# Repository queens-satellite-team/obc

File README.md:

# OBC0
### Overview
The OBC0 is based on a Arm Cortex M4 and uses a
[STM32 Nucleo-F446RE](https://www.digikey.ca/en/products/detail/stmicroelectronics/NUCLEO-F446RE/5347712)
development board. The documentation for the Nucleo board is [here](). This
Nucleo board wasn't chosen for a specific reason, and it is possible in future
we will switch a different one. The Nucleo development board family was selected
for ease of development and having a built in ST-Link programmer.

### Directory Structure

### Building
The repository is configured to build with the GNU Arm Embedded Toolchain and
CMake. In a Unix-like environment, open a termina, navigate to the root of the
repository and run:
```
mkdir build && cd build
cmake -DCMAKE_TOOLCHAIN_FILE=../arm-none-eabi-gcc.cmake -DCMAKE_BUILD_TYPE=Debug ..
cmake --build . -- -j 4
```
To flash the executable to the Nucleo:
```
sudo st-flash write <name-of-executable>.bin 0x8000000
```
### Notes
To get the `stm32f4xx_hal_i2c` driver to compile, it was necessary to define
a `HAL_I2C_WRONG_START` variable which was set arbitrarily to 0. This seems to
be a known [issue](https://github.com/STMicroelectronics/STM32CubeG4/issues/8)
with the library.

this is a test change!

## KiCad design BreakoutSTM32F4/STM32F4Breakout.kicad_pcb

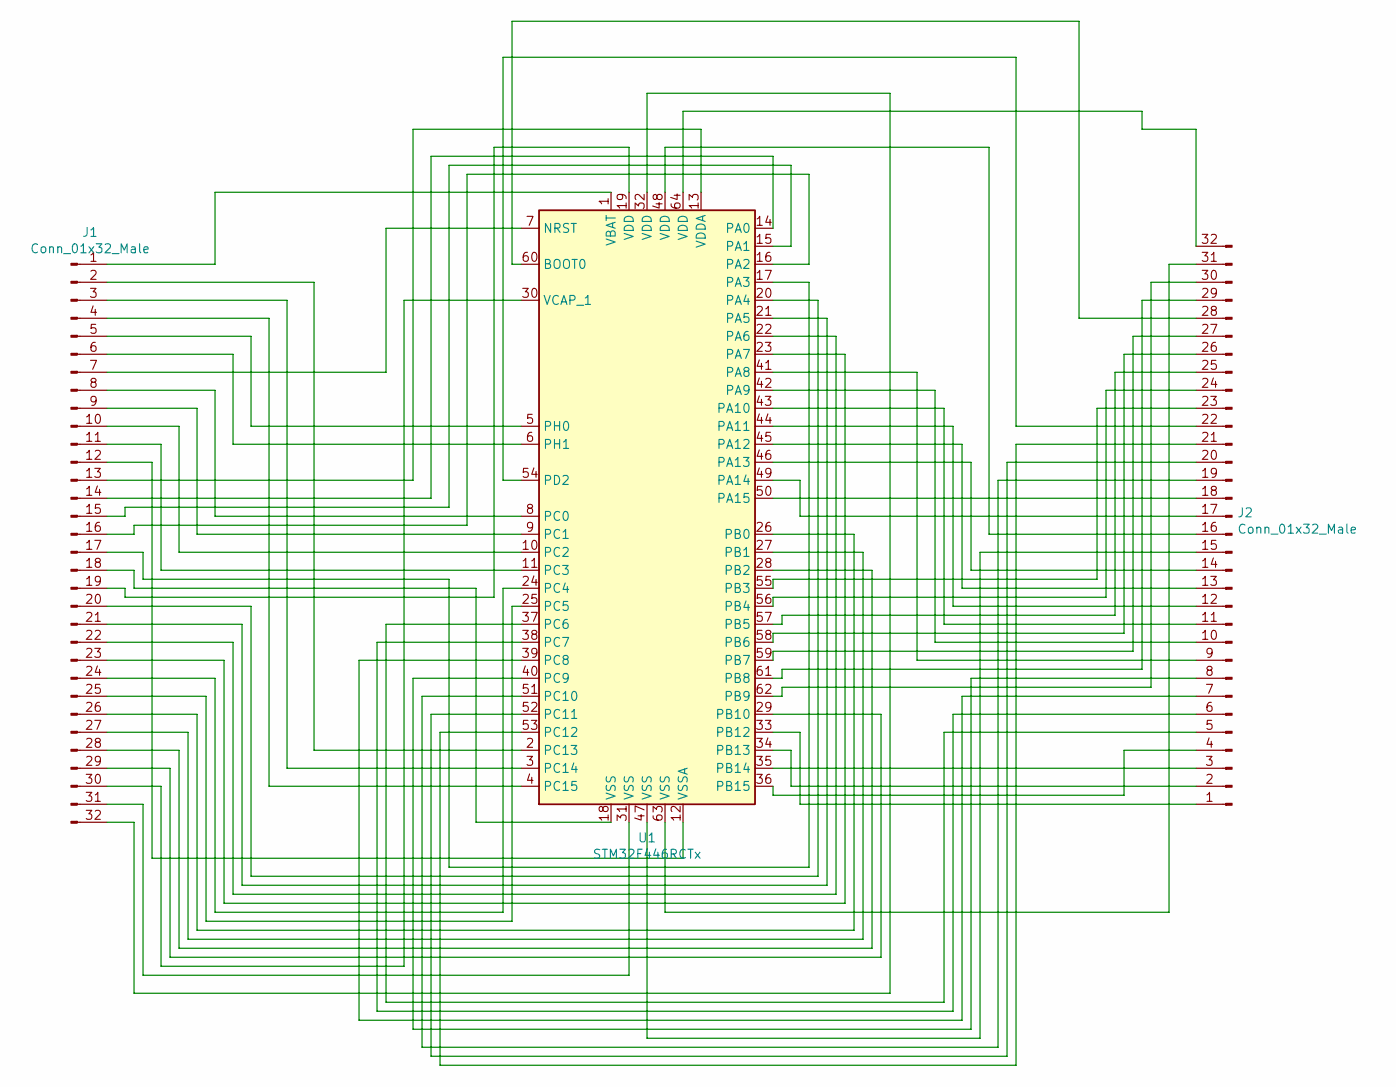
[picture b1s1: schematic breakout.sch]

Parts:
J1, J2: Conn_01x32_Male; PinSocket_1x32_P2.54mm_Vertical
U1: STM32F446RCTx; LQFP-64_10x10mm_P0.5mm

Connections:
unnamed: J1.1, U1.1 (VBAT)
unnamed: J1.2, U1.2 (PC13)
unnamed: J1.3, U1.3 (PC14)
unnamed: J1.4, U1.4 (PC15)
unnamed: J1.5, U1.5 (PH0)
unnamed: J1.6, U1.6 (PH1)
unnamed: J1.7, U1.7 (NRST)
unnamed: J1.8, U1.8 (PC0)
unnamed: J1.9, U1.9 (PC1)
unnamed: J1.10, U1.10 (PC2)
unnamed: J1.11, U1.11 (PC3)
unnamed: J1.12, U1.12 (VSSA)
unnamed: J1.13, U1.13 (VDDA)
unnamed: J1.14, U1.14 (PA0)
unnamed: J1.15, U1.15 (PA1)
unnamed: J1.16, U1.16 (PA2)
unnamed: J1.17, U1.17 (PA3)
unnamed: J1.18, U1.18 (VSS)
unnamed: J1.19, U1.19 (VDD)
unnamed: J1.20, U1.20 (PA4)
unnamed: J1.21, U1.21 (PA5)
unnamed: J1.22, U1.22 (PA6)
unnamed: J1.23, U1.23 (PA7)
unnamed: J1.24, U1.24 (PC4)
unnamed: J1.25, U1.25 (PC5)
unnamed: J1.26, U1.26 (PB0)
unnamed: J1.27, U1.27 (PB1)
unnamed: J1.28, U1.28 (PB2)
unnamed: J1.29, U1.29 (PB10)
unnamed: J1.30, U1.30 (VCAP_1)
unnamed: J1.31, U1.31 (VSS)
unnamed: J1.32, U1.32 (VDD)
unnamed: J2.1, U1.33 (PB12)
unnamed: J2.2, U1.34 (PB13)
unnamed: J2.3, U1.35 (PB14)
unnamed: J2.4, U1.36 (PB15)
unnamed: J2.5, U1.37 (PC6)
unnamed: J2.6, U1.38 (PC7)
unnamed: J2.7, U1.39 (PC8)
unnamed: J2.8, U1.40 (PC9)
unnamed: J2.9, U1.41 (PA8)
unnamed: J2.10, U1.42 (PA9)
unnamed: J2.11, U1.43 (PA10)
unnamed: J2.12, U1.44 (PA11)
unnamed: J2.13, U1.45 (PA12)
unnamed: J2.14, U1.46 (PA13)
unnamed: J2.15, U1.47 (VSS)
unnamed: J2.16, U1.48 (VDD)
unnamed: J2.17, U1.49 (PA14)
unnamed: J2.18, U1.50 (PA15)
unnamed: J2.19, U1.51 (PC10)
unnamed: J2.20, U1.52 (PC11)
unnamed: J2.21, U1.53 (PC12)
unnamed: J2.22, U1.54 (PD2)
unnamed: J2.23, U1.55 (PB3)
unnamed: J2.24, U1.56 (PB4)
unnamed: J2.25, U1.57 (PB5)
unnamed: J2.26, U1.58 (PB6)
unnamed: J2.27, U1.59 (PB7)
unnamed: J2.28, U1.60 (BOOT0)
unnamed: J2.29, U1.61 (PB8)
unnamed: J2.30, U1.62 (PB9)
unnamed: J2.31, U1.63 (VSS)
unnamed: J2.32, U1.64 (VDD)

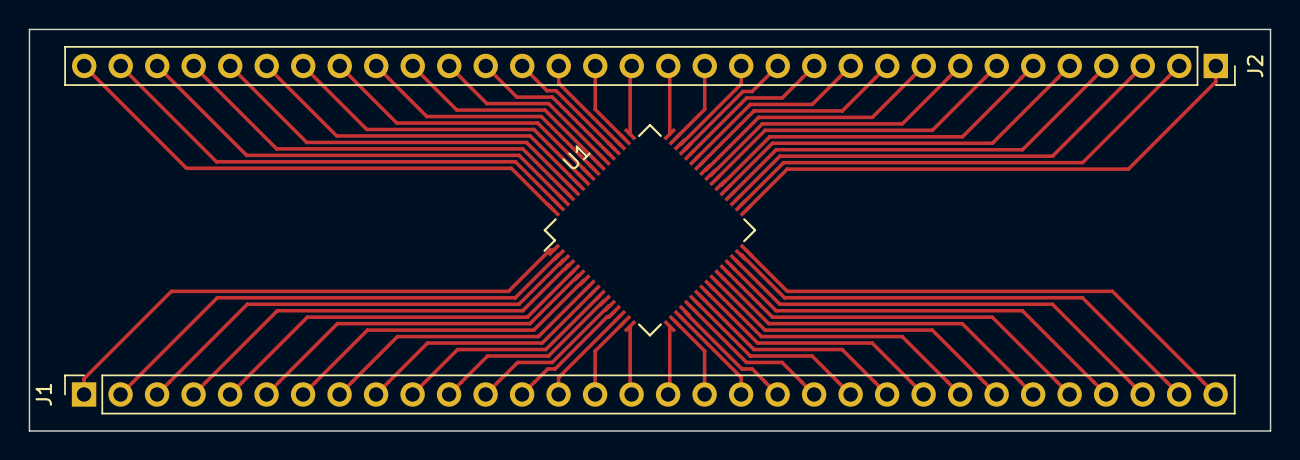
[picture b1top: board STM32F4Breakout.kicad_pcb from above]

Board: 2 copper layers, 86.4 x 27.9 mm, 3 parts (0 on the bottom side), 64 nets.

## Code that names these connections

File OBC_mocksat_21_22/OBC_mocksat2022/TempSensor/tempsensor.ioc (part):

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Mcu.Name=STM32G0B1R(B-C-E)Tx
Mcu.Package=LQFP64
Mcu.UserName=STM32G0B1RETx
PB8.Mode=I2C
PB8.Signal=I2C1_SCL
PB9.Mode=I2C
PB9.Signal=I2C1_SDA
PC0.Mode=Asynchronous
PC0.Signal=LPUART1_RX
PC1.Mode=Asynchronous
PC1.Signal=LPUART1_TX
PC11.Signal=GPIO_Output
RCC.HSE_VALUE=8000000
RCC.SYSCLKFreq_VALUE=16000000
board=custom

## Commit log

2020-02-28 Add /Common and contents
2020-02-28 Add BSP Driver
2020-02-28 Add CMSIS driver
2020-02-28 Create placeholder.md to create Drivers dir
2020-07-24 Move stm320xx and stm_tutorial repos here
2020-07-25 Tar ball old repo code for use later
2020-07-27 Remove empty directory
2020-07-29 Compile and flash basic LED blink example on Linux
    The LED example is not working. The instructions for the CMakeLists.txt
    I got from this tutorial https://dev.to/younup/cmake-on-stm32-the-beginning-3766.
    I also got the directory structure from this template code
    https://github.com/andreassinn/STM32F446-Nucleo-Template/tree/master/Src.
    The code has only been compiled and flashed on Linux.
2020-07-29 Complete 6de5080, not all files pushed
    Accidently used git add from a non-root directory so not all files were commited
2020-07-29 Add explanation for Nucleo board choice to README
2022-06-10 Added 21-22 mocksat code
    Moved mocksat code from other repositories and put inside one folder. Still needs to be organized within OBC repo.
2022-09-27 readme: run test to verify pushing credentials
2022-09-27 file cleanup
2022-09-28 task folders
2022-10-12 added simulations
2022-12-31 Implement RTC Driver code for Raspberry Pi
2023-01-09 Created software watchdog manager
2023-01-15 Create subsystem class files, comment out instructions on I2c
2023-01-15 creates adcs class skeleton with examples
2023-01-15 created example class with syntax examples
2023-01-15 create adcs class file
2023-01-15 create comms class file
2023-01-15 create eps class file
2023-01-15 create satellite class file
2023-01-15 classwide docstring
2023-01-18 OBC: structure and description for ground, fault, pass isr's
2023-01-25 adds skeleton for interrupt service routines
2023-01-28 groups 'events' and 'tasks' files, imports isrs into eventmanager
2023-01-28 adds 'pass' to the subsystem classes to prevent errors
2023-01-28 creates methods and outlines specific objectives for each
2023-01-28 Updates outline comments in default_ISRs
2023-01-28 fixes r/s prefix
2023-01-28 Saying hi
2023-01-28 conflict test
2023-01-28 creates a requirements.txt file for package installation
2023-02-07 Create code
2023-02-08 First ideas on i2c r/t methods
2023-02-11 First pass at get_requestTS
2023-02-11 clean up
2023-02-14 Create Katherine-power-code
2023-02-15 i2c write/read code example
2023-02-19 Begin ADC interface developement
2023-02-19 remove duplicate
2023-03-01 COMMS: adds high level transmit/receive data logic
2023-03-04 bug fixes and renaming
2023-03-11 added pyserial to requirements.txt
2023-03-11 adds serial communication code (commented), needs testing
2023-05-10 notes that this is untested functionality
2023-05-24 README: create initial README
2023-05-25 stm32 support
2023-05-29 add obc_controller implementation
2023-05-29 fix obc contoller
2023-05-29 fix rwheels
2023-08-05 adds yaml file for github workflow triggering
2023-08-05 includes a dummy test file, a dummy method to test, adds pytest to requirements
2023-08-05 trying to fix the python version issue
